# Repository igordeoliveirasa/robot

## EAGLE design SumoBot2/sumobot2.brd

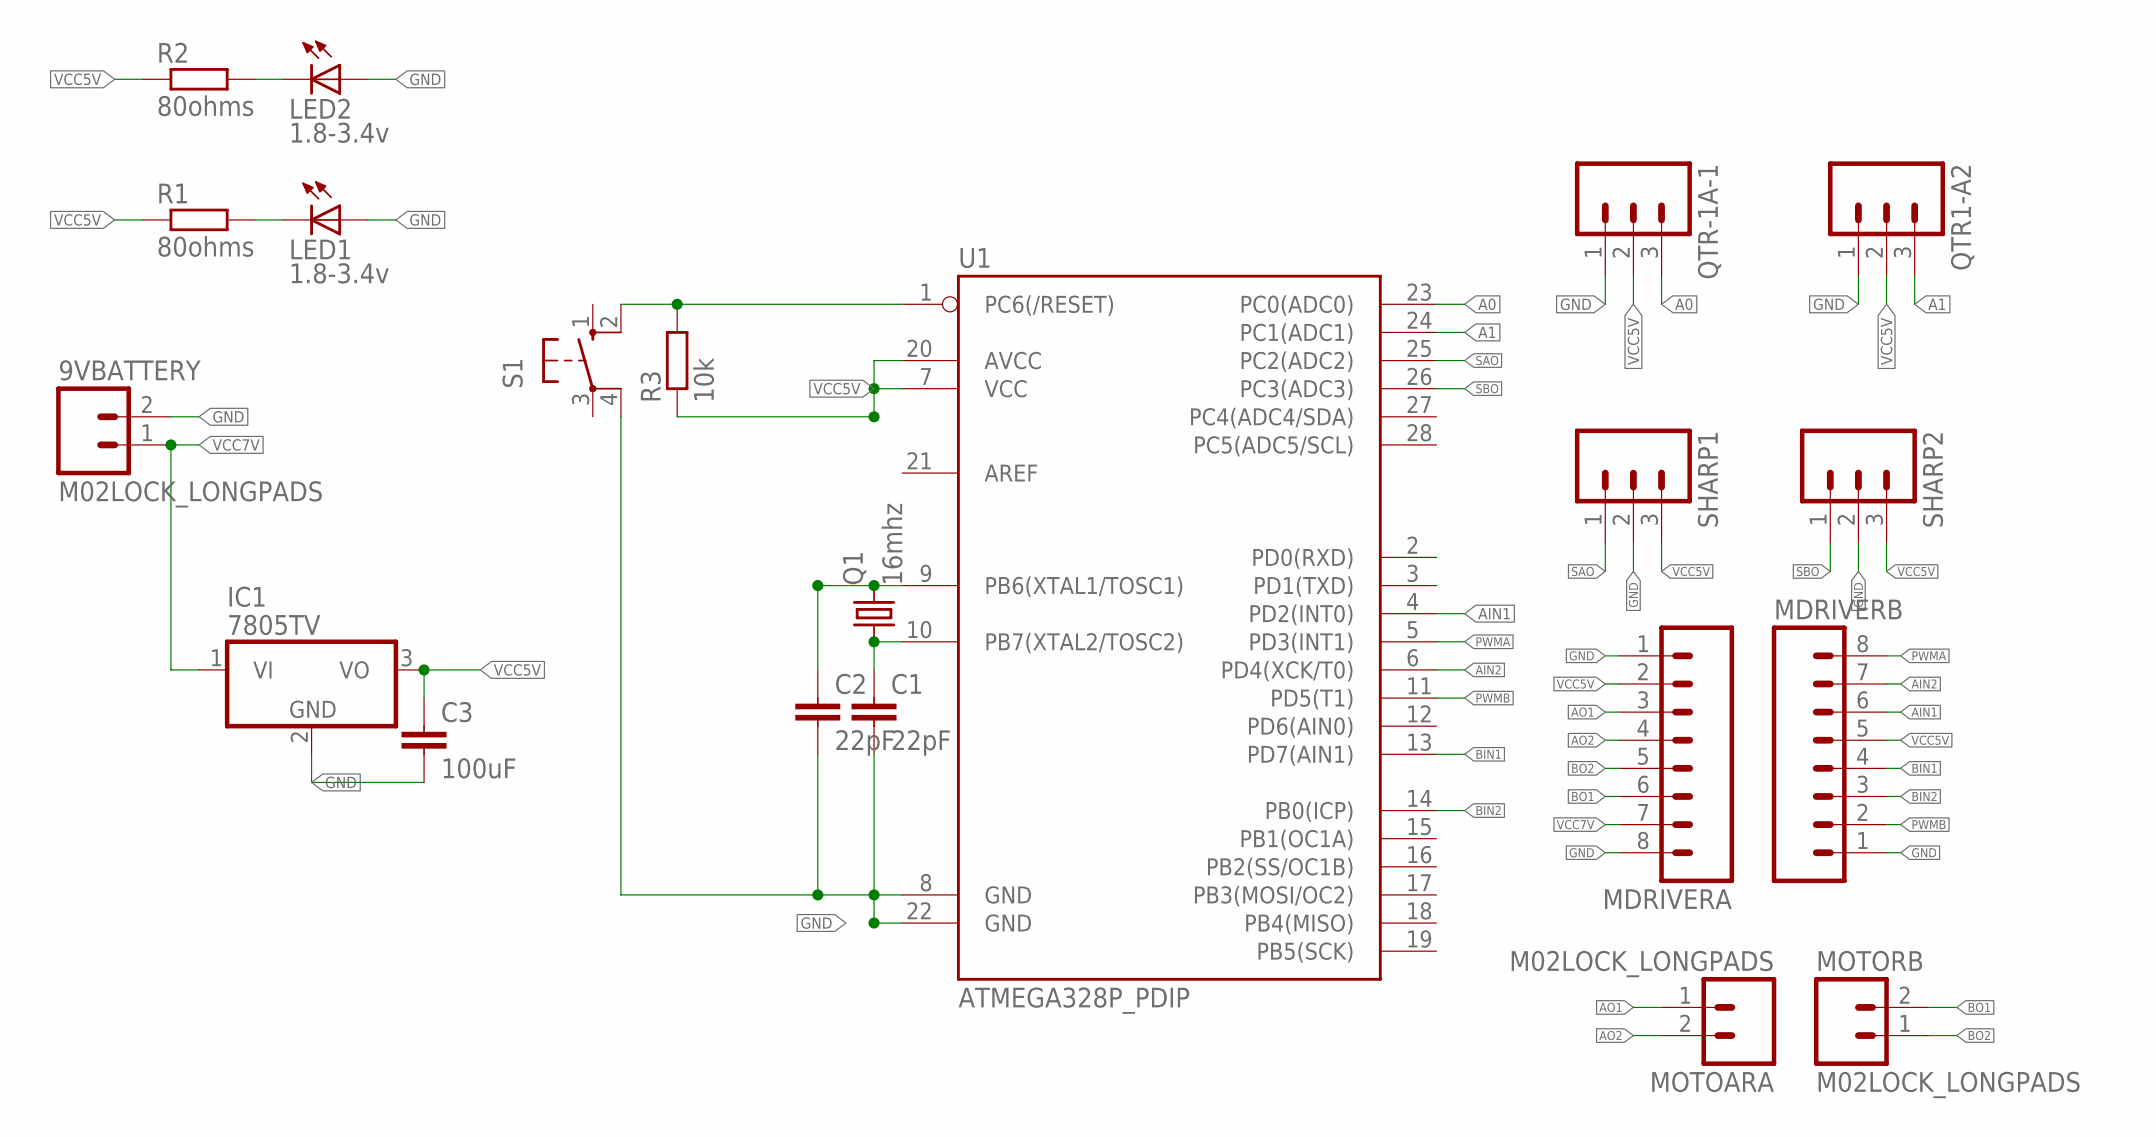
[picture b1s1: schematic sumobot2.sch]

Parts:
9VBATTERY: M02LOCK_LONGPADS; 1X02_LOCK_LONGPADS
C1, C2: 22pF; C025-025X050
C3: 100uF; C025-025X050
IC1: 7805TV; TO220V
LED1, LED2: 1.8-3.4v; LED3MM
MDRIVERA: M08LONGPADS; 1X08_LONGPADS
MDRIVERB: M08LONGPADS; 1X08_LONGPADS
MOTOARA: M02LOCK_LONGPADS; 1X02_LOCK_LONGPADS
MOTORB: M02LOCK_LONGPADS; 1X02_LOCK_LONGPADS
Q1: 16mhz; HC49U70
QTR1-A2: M03LONGPADS; 1X03_LONGPADS
QTR-1A-1: M03LONGPADS; 1X03_LONGPADS
R1, R2: 80ohms; 0207/10
R3: 10k; 0207/10
S1: 10-XX; B3F-10XX
SHARP1, SHARP2: M03LONGPADS; 1X03_LONGPADS
U1: ATMEGA328P_PDIP; DIL28-3

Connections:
A0: QTR-1A-1.3, U1.23 (PC0(ADC0))
A1: QTR1-A2.3, U1.24 (PC1(ADC1))
AIN1: MDRIVERB.6, U1.4 (PD2(INT0))
AIN2: MDRIVERB.7, U1.6 (PD4(XCK/T0))
AO1: MDRIVERA.3, MOTOARA.1
AO2: MDRIVERA.4, MOTOARA.2
BIN1: MDRIVERB.4, U1.13 (PD7(AIN1))
BIN2: MDRIVERB.3, U1.14 (PB0(ICP))
BO1: MDRIVERA.6, MOTORB.2
BO2: MDRIVERA.5, MOTORB.1
GND: 9VBATTERY.2, C1.2, C2.2, C3.2, IC1.2 (GND), LED1.A, LED2.A, MDRIVERA.1, MDRIVERA.8, MDRIVERB.1, QTR1-A2.1, QTR-1A-1.1, S1.4 (P1), SHARP1.2, SHARP2.2, U1.8 (GND), U1.22 (GND)
unnamed: C2.1, Q1.2, U1.9 (PB6(XTAL1/TOSC1))
unnamed: LED1.K (C), R1.2
unnamed: C1.1, Q1.1, U1.10 (PB7(XTAL2/TOSC2))
unnamed: R3.2, S1.2 (S1), U1.1 (PC6(/RESET))
unnamed: LED2.K (C), R2.2
PWMA: MDRIVERB.8, U1.5 (PD3(INT1))
PWMB: MDRIVERB.2, U1.11 (PD5(T1))
SAO: SHARP1.1, U1.25 (PC2(ADC2))
SBO: SHARP2.1, U1.26 (PC3(ADC3))
VCC5V: C3.1, IC1.3 (VO), MDRIVERA.2, MDRIVERB.5, QTR1-A2.2, QTR-1A-1.2, R1.1, R2.1, R3.1, SHARP1.3, SHARP2.3, U1.7 (VCC), U1.20 (AVCC)
VCC7V: 9VBATTERY.1, IC1.1 (VI), MDRIVERA.7

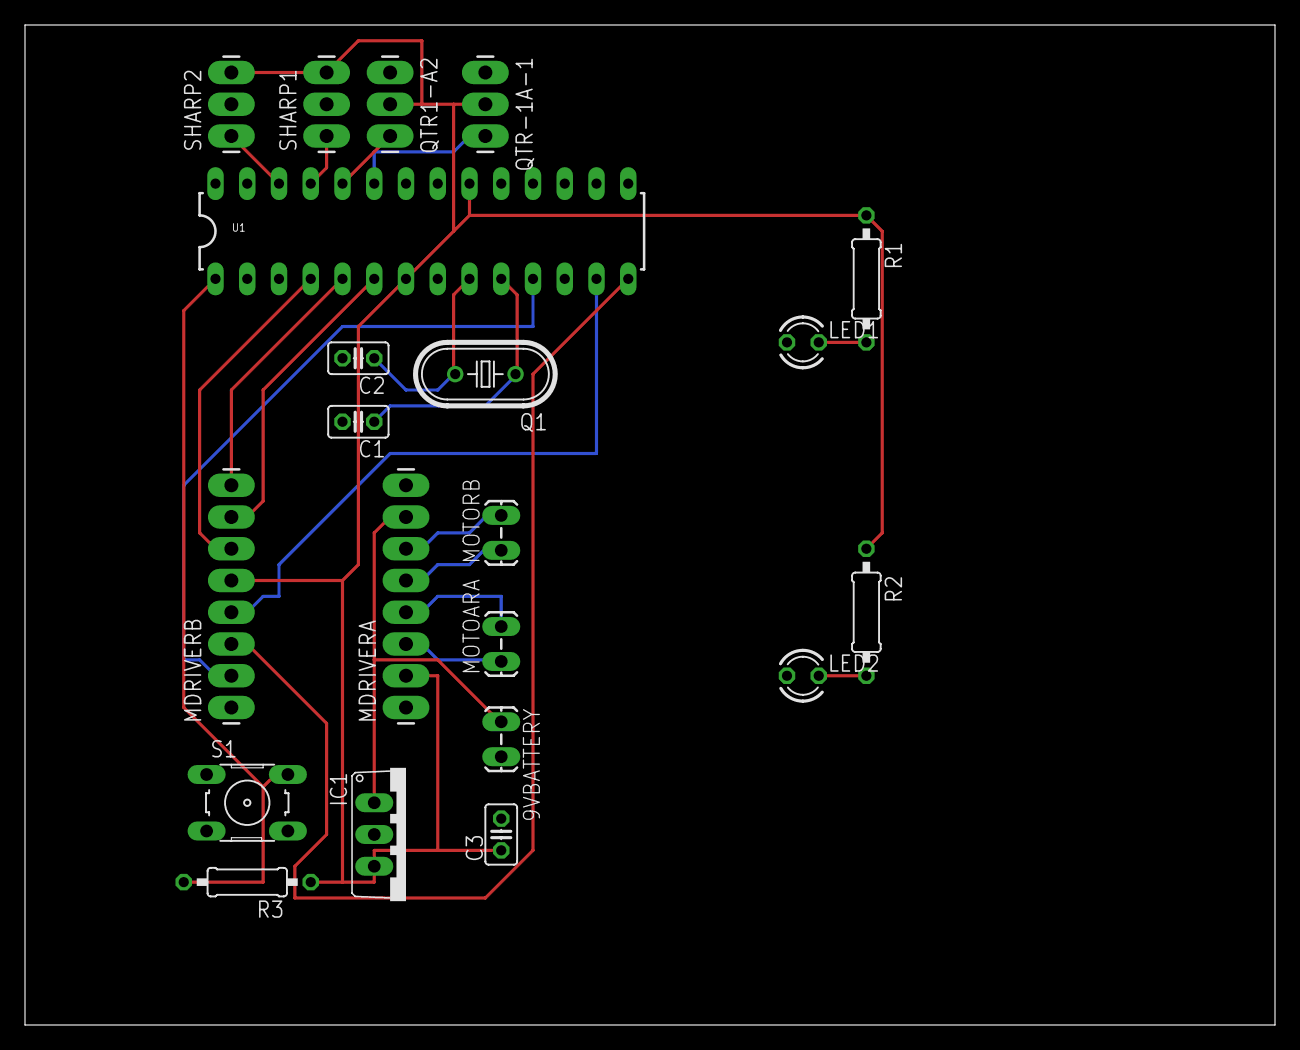
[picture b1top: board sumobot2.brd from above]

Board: 2 copper layers, 100.0 x 80.0 mm, 21 parts (0 on the bottom side), 22 nets.

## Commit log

2014-01-31 kick-off
2014-02-11 java
2014-02-16 joystick

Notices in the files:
parts and their libraries:
SparkFun-DigitalIC: Licensing: Creative Commons ShareAlike 4.0 International - https://creativecommons.org/licenses/by-sa/4.0
